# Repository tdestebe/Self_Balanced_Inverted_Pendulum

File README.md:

# Self_Balanced_Inverted_Pendulum

Self Balanced Inverted Pendulum

This project aims to build an inverted pendulum stabilized by a single reaction wheel. The position of the pendulum is detected by a 3-axis analog gyroscope sensor (MPU6050 module). The position is analyzed inside an Arduino Nano that sends appropriate signals to a motor (Nidec 24H404H160). 

## 3D CAD Model

The assembly of the CAD models and parts are designed with FreeCAD. Following worbenchs are used:

- **Part design** to design 3D mechanical parts

- **Assembly 4.1** based on local axis systems

- **Fasteners** for all screws and nuts

- **Mesh** to create and export STL files

**Inverted pendulum - FreeCAD mesh export**

FreeCAD files are available at [freeCad](https://github.com/tdestebe/Self_Balanced_Inverted_Pendulum/tree/main/freeCad)

STL 3D files are at [STL_files](https://github.com/tdestebe/Self_Balanced_Inverted_Pendulum/tree/main/STL_files)

## Simulation with openModelica

Simulation is performed through an openModelica implementation into the package SelfBalancedWheelPackage. Main Modelica model **SingleWheelRobot** calls model **Dynamics** in which PID, Motor, etc are implemented and calls model **Animation** to display rotation of 3D models of the reaction wheel and the arm. 

**Inverted pendulum - Modelica main model**

<table border="0" style="width: 100%;">
  <!-- Current Row -->
  <tr>
    <th style="border: none; text-align: center; font-weight: bold;"></th>
    <th style="border: none; text-align: center; font-weight: bold;"></th>
    <th style="border: none; text-align: center; font-weight: bold;"></th>
  </tr>
  <!-- Header Rows -->
  <tr>
    <td style="border: none;"><b>Inverted pendulum - Modelica Dynamics model</b></td>
    <td style="border: none; text-align: center; font-weight: bold;"></td>
    <td style="border: none;"><b>Inverted pendulum - Modelica Animation model</b></td>
  </tr>
</table>

Source files are available at [Self Balaced Wheel Package](https://github.com/tdestebe/Self_Balanced_Inverted_Pendulum/tree/main/SelfBalancedWheelPackage)

## Arduino code and circuits

### Code (.ino)

The source code for Arduino is provided at [code](https://github.com/tdestebe/Self_Balanced_Inverted_Pendulum/tree/main/code). It is similar to the code written by **Remigijus** (see [remrc - One-Axis-Reaction-Wheel-Stick](https://github.com/remrc/One-Axis-Reaction-Wheel-Stick)).

### Fritzing schema

The schema is also identical to the original one posted by Remigijus. I just rewrote it with Fritzing, including a breadboard and stored the source at [circuit](https://github.com/tdestebe/Self_Balanced_Inverted_Pendulum/tree/main/circuit).

<table border="0" style="width: 100%;">
  <!-- Current Row -->
  <tr>
    <th style="border: none; text-align: center; font-weight: bold;"></th>
    <th style="border: none; text-align: center; font-weight: bold;"></th>
    <th style="border: none; text-align: center; font-weight: bold;"></th>
  </tr>
  <!-- Header Rows -->
  <tr>
    <td style="border: none;"><b>Fritzing schema - Original</b></td>
    <td style="border: none; text-align: center; font-weight: bold;"></td>
    <td style="border: none;"><b>Fritzing schema - Breadboard</b></td>
  </tr>
</table>

### KiCad circuit

In addition to Fritzing schema, I implemented KiCad schematic circuit and generated a KiCad PCB for visualisation into the 3D CAD assembly. 

Kicad project is stored at [kiCAD](https://github.com/tdestebe/Self_Balanced_Inverted_Pendulum/tree/main/kiCAD).

<table border="0" style="width: 100%;">
  <!-- Current Row -->
  <tr>
    <th style="border: none; text-align: center; font-weight: bold;"></th>
    <th style="border: none; text-align: center; font-weight: bold;"></th>
    <th style="border: none; text-align: center; font-weight: bold;"></th>
  </tr>
  <!-- Header Rows -->
  <tr>
    <td style="border: none;"><b>KiCad circuit - Schema</b></td>
    <td style="border: none; text-align: center; font-weight: bold;"></td>
    <td style="border: none;"><b>KiCad circuit - PCD 3D view</b></td>
  </tr>
</table>

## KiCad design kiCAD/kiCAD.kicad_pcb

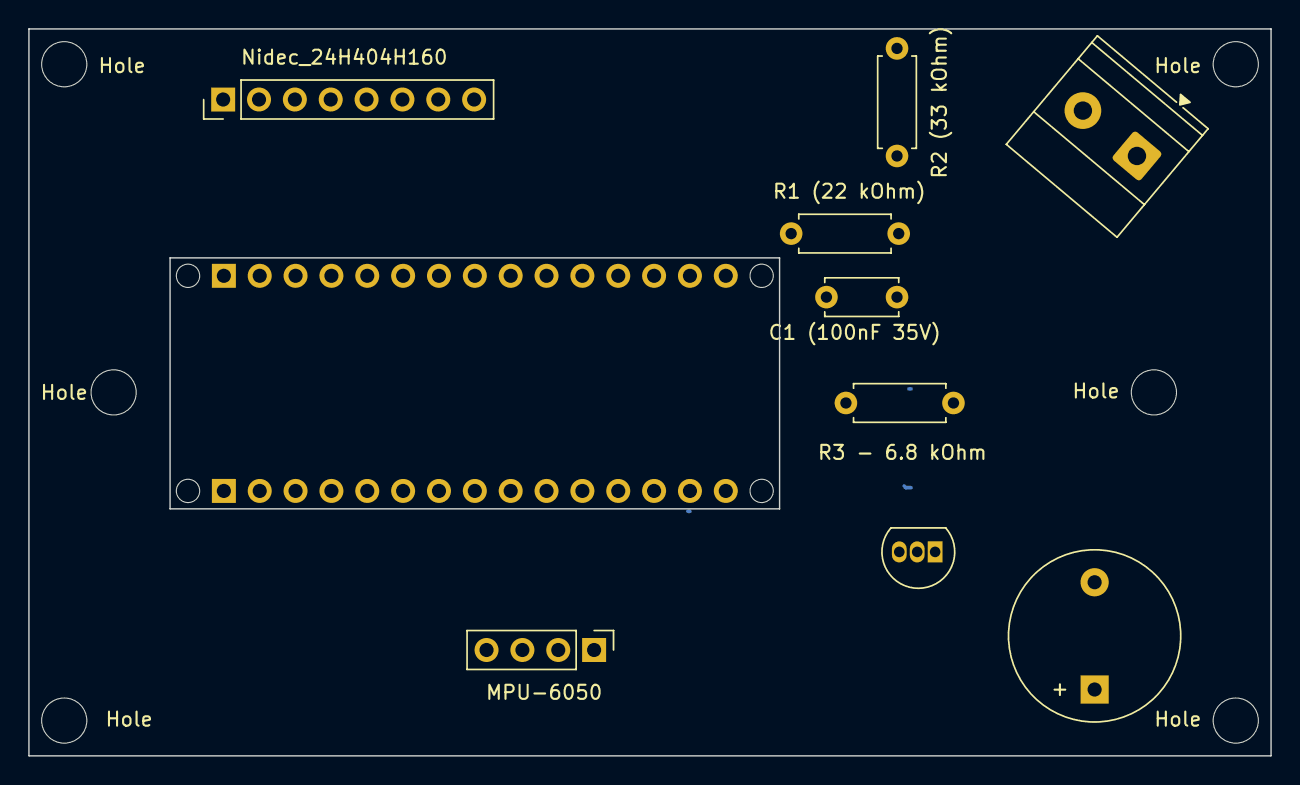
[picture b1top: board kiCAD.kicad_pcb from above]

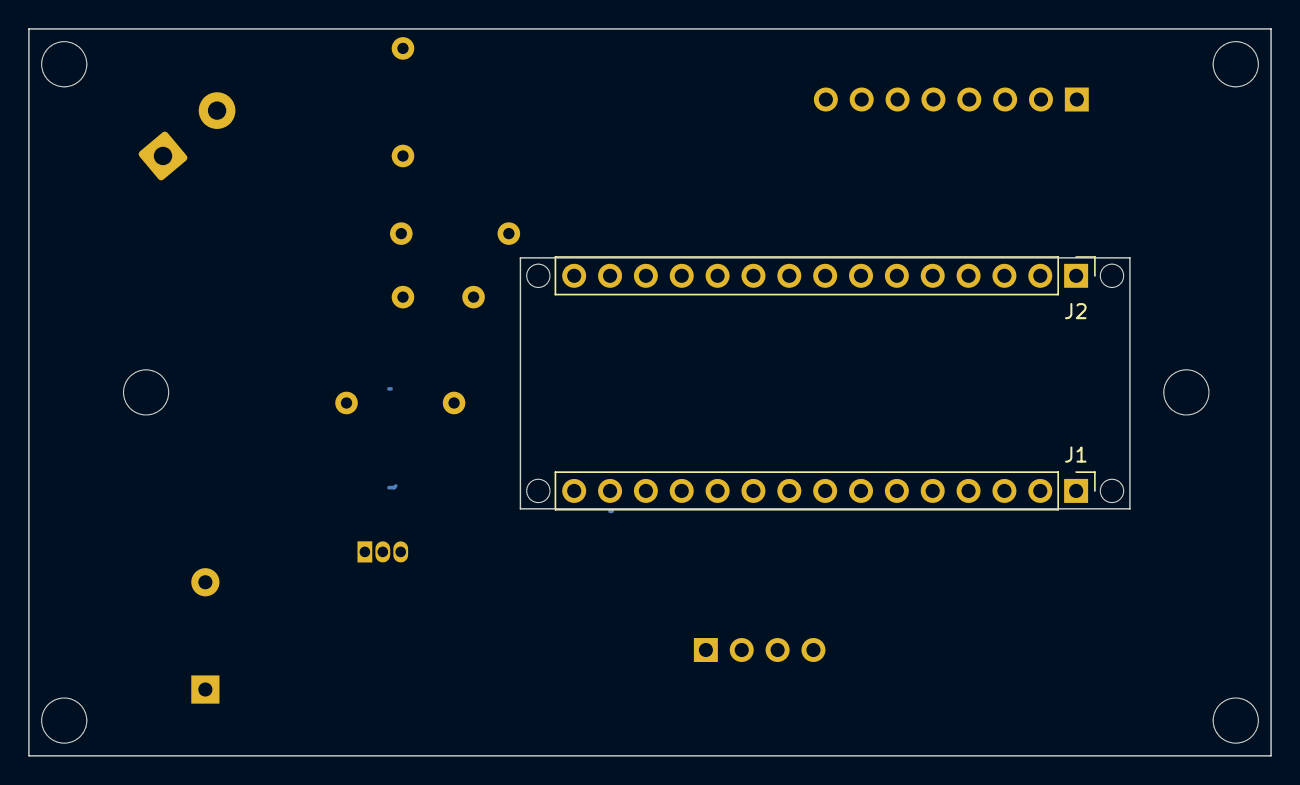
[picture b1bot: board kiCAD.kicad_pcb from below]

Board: 2 copper layers, 88.0 x 51.5 mm, 21 parts (2 on the bottom side), 13 nets.

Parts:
500 mAh  Lipo 11.1 V: Battery 500 mAh Lipo (11.1 V); TerminalBlock_Phoenix_MKDS-1,5-2_1x02_P5.00mm_Horizontal
BZ1 (Buzzer 5V): Buzzer 5V; Buzzer_12x9.5RM7.6
C1 (100nF 35V): 100nF 35V; C_Disc_D5.0mm_W2.5mm_P5.00mm
Hole: 3.6mm; MountingHole_3.2mm
Hole#2, Hole#3, Hole#4, Hole#6: 2.6mm; MountingHole_3.2mm
Hole#5: 3.6mm; MountingHole_3.2mm
J1: Analog; PinHeader_1x15_P2.54mm_Vertical
J2: Digital; PinHeader_1x15_P2.54mm_Vertical
MH1, MH2, MH3, MH4: MountingHole_65mil
MPU-6050: PinHeader_1x04_P2.54mm_Vertical
Nidec_24H404H160: PinHeader_1x08_P2.54mm_Vertical
Q1 (2N2222 - BC547): 2N2222; TO-92L_Inline
R1 (22 kOhm): 22 kOhm; R_Axial_DIN0207_L6.3mm_D2.5mm_P7.62mm_Horizontal
R2 (33 kOhm): 33 kOhm; R_Axial_DIN0207_L6.3mm_D2.5mm_P7.62mm_Horizontal
R3 - 6.8 kOhm: 6.8 kOhm; R_Axial_DIN0207_L6.3mm_D2.5mm_P7.62mm_Horizontal

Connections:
+5V: BZ1 (Buzzer 5V).1 (+), J1.12, MPU-6050.1 (VCC)
/*D9: J2.4, Nidec_24H404H160.4 (PWM)
/A4/SDA: J1.8, MPU-6050.4 (SDA)
/A5/SCL: J1.9, MPU-6050.3 (SCL)
/A7: C1 (100nF 35V).1, J1.11, R1 (22 kOhm).1, R2 (33 kOhm).2
/D4: J2.9, Nidec_24H404H160.5 (Direction)
/D8: J2.5, Nidec_24H404H160.3 (Start/Stop)
/D12/MISO: J2.1, R3 - 6.8 kOhm.2
/~RESET: J1.13, J2.13
GND: 500 mAh Lipo 11.1 V.2 (-), C1 (100nF 35V).2, J1.14, J2.12, MPU-6050.2 (GND), Nidec_24H404H160.2 (GND), Q1 (2N2222 - BC547).2 (B), R1 (22 kOhm).2
unnamed: BZ1 (Buzzer 5V).2 (-), Q1 (2N2222 - BC547).3 (C)
unnamed: Q1 (2N2222 - BC547).1 (E), R3 - 6.8 kOhm.1
VCC: 500 mAh Lipo 11.1 V.1 (+), J1.15, Nidec_24H404H160.1 (+12V), R2 (33 kOhm).1

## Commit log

2026-01-04 Create pendulum_Arm.FCStd
    Initial CAD arm file.
2026-01-04 Create .gitignore
    Ignore freeCad backup files
2026-01-04 Added CAD models
    Bearing ball created and pendulum arm updated.
2026-01-04 Create motor_Nidec_24H.FCStd
    Created CAD model of Nidec 24H motor.
2026-01-06 Created initial assembly
    Added some 3D components and created initial assembly with.
2026-01-07 Added MPU6050 module
    Created and added MPU6050 CAD model into assembly.
2026-01-07 Update assembly_Pendulum.FCStd
    Added some screws
2026-01-08 Added screws and exported Arm
    Added screws into the assembly and exported CAD model of Arm in STL file
2026-01-08 Updated assembly and exported 3D view
    Screws are up-to-date and I exported a 3D view.
2026-01-10 Modified design
    Arm design modified for a better link with bearing.
2026-01-12 adapted dimensions
    Modified 3D model with more convenient dimensions.
2026-01-12 Next step
    Prepare next files
2026-01-13 Added Arduino stuff
    Added Arduino Nano CAD model and box.
2026-01-15 re-organize folder
    Export modified CAD models from the assembly. Delete old obsolete ones.
2026-01-15 Created battery holder
    Created CAD model of battery holder and assembled it with battery
2026-01-20 Added foot for pendulum
    Added a foot to fix pendulum
2026-01-20 Minor change
    Minor change before next step
2026-01-21 Added pedestral 3D CAD model
    Added a full pedestal to support inverted pendulum.
2026-01-21 Update README.md
    Added picture (3D model)
2026-01-21 Update README.md
    Minor typo fixed
2026-01-22 Update README.md
    Changed image dimension settings
2026-01-22 Added animation
    Created a variable to animate the assembly. Arm can balance from -12° to 12°.
2026-01-22 Added circuit
    Added Fritzing file with Arduino based circuit and its exported view.
2026-01-23 Tested scew in Assembly
    Screw group can move to Assembly for animations.
2026-01-24 added main arduino code
    Same as in https://github.com/remrc/One-Axis-Reaction-Wheel-Stick
2026-01-31 Added Circuit
    Added electronic parts to CAD models
2026-01-31 Updated assembly
    Updated assembly with circuit and box.
2026-02-02 Updated assembly
    Modified circuit box with a hole for axial screw.
2026-02-03 Added KiCad project
    Added kiCad files with schematics and 3D view of Arduino circuits. PCB design not complete.
2026-02-04 Minor update
    Updated transitor name with BC547
2026-02-12 Completed hardware and run
    Hardware is complete with breadboard. CAD assembly is complete as well.
    Arduino code is almost tuned so that inverted pendulum is self balanced.
2026-02-14 Simulation running
    Complete CAD model added to simulation with openModelica.
2026-02-17 Updated simulation
    Modified simulation for more realistic rotation of reaction wheel.
    Added CAD model of a button and its holder.
    Minor changes on STL files.
2026-02-18 Added SVG images and updated README
    Added views from Modelica.
2026-02-18 Update README.md
    Simulation paragraph
2026-02-18 Update README.md with simulation part
2026-02-18 Added schema
    New Fritzing schematics with breadboard.
2026-02-18 Exported picture for README
    Did some clean up and exported view to illustrate circuits.
2026-02-18 Minor changes
    Picture format to PNG and fixed typo into README.
2026-02-19 FreeCad repository clean up
    Updated freeCad files from Assembly to individual files.
2026-02-19 Simulation setup
    Change simulation set up in openModelica.
2026-02-19 Update README.md
    Typo
2026-03-06 New button design
    Circular button holder.
2026-04-04 Updated models
    Updated models to figure out last improvements.
2026-04-04 Updated 3D view
    Modified picture used for presentation.
2026-04-04 Changed 3D view
    Changed 3D view background and orientation.
